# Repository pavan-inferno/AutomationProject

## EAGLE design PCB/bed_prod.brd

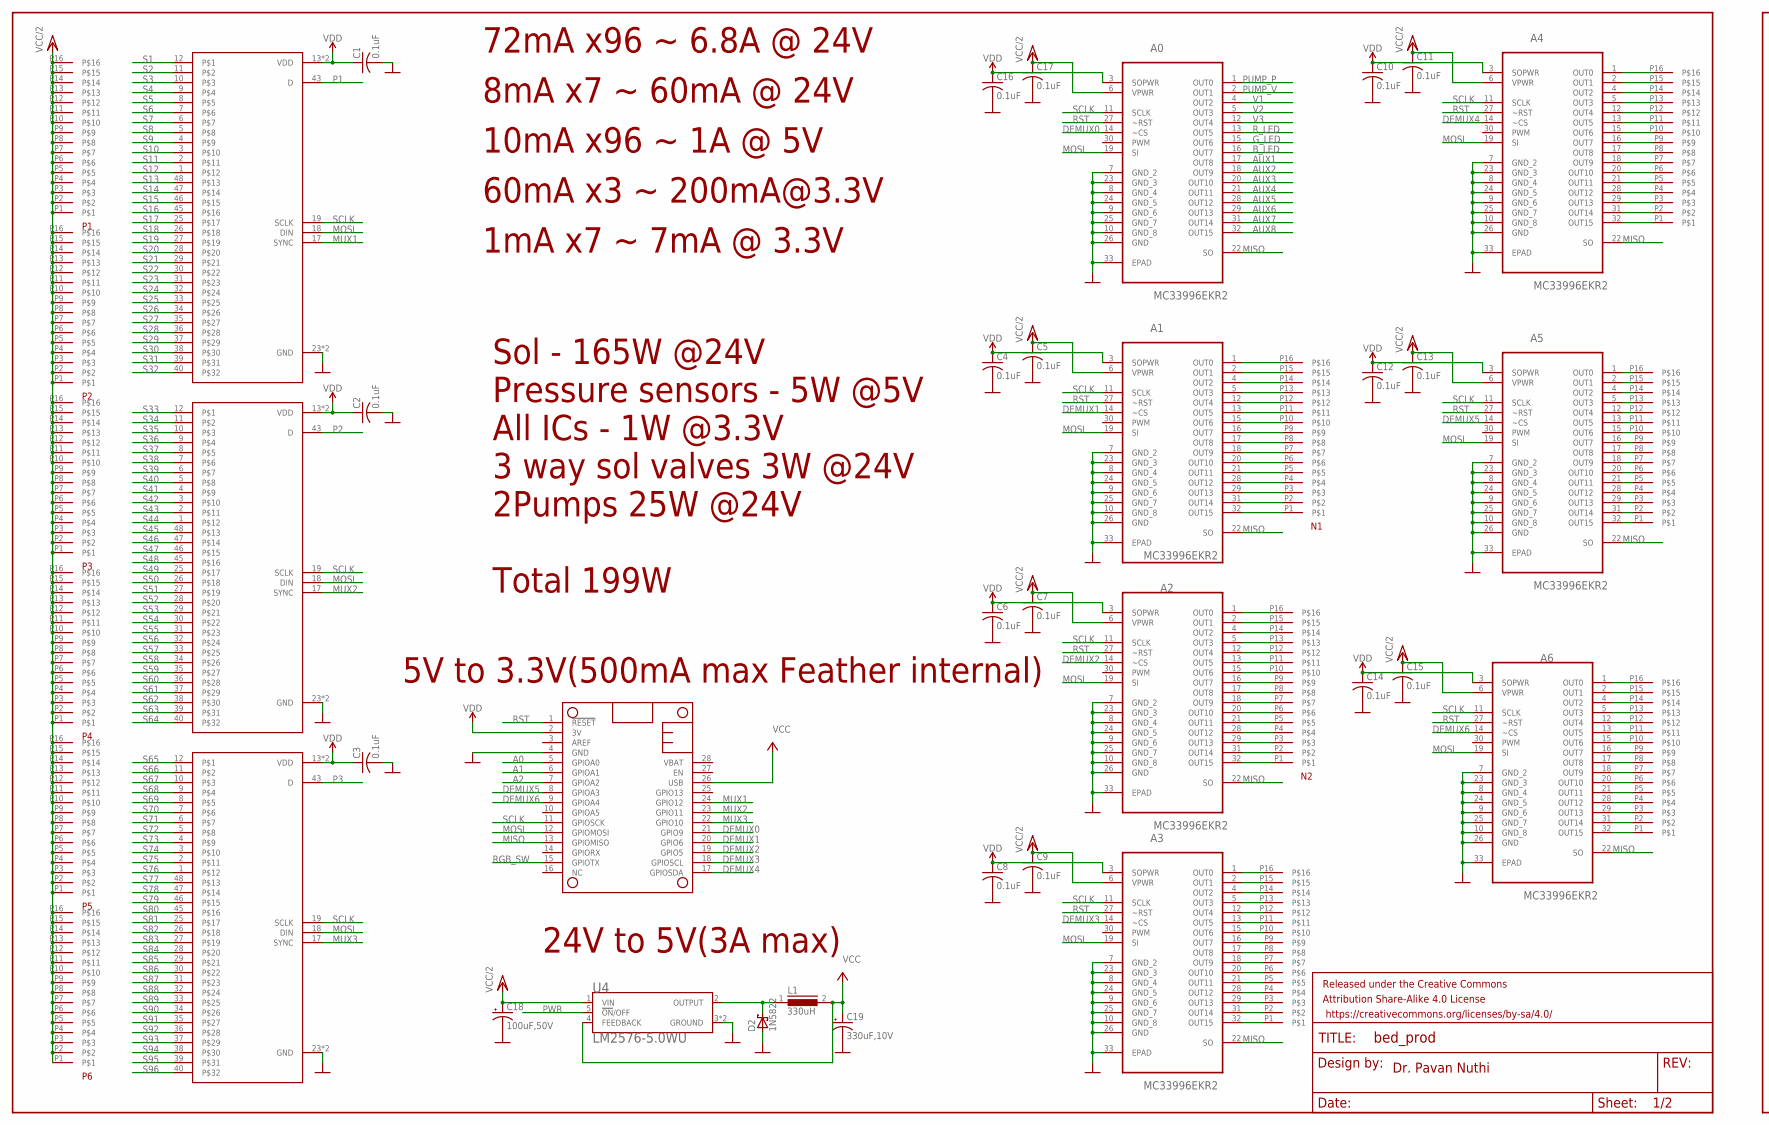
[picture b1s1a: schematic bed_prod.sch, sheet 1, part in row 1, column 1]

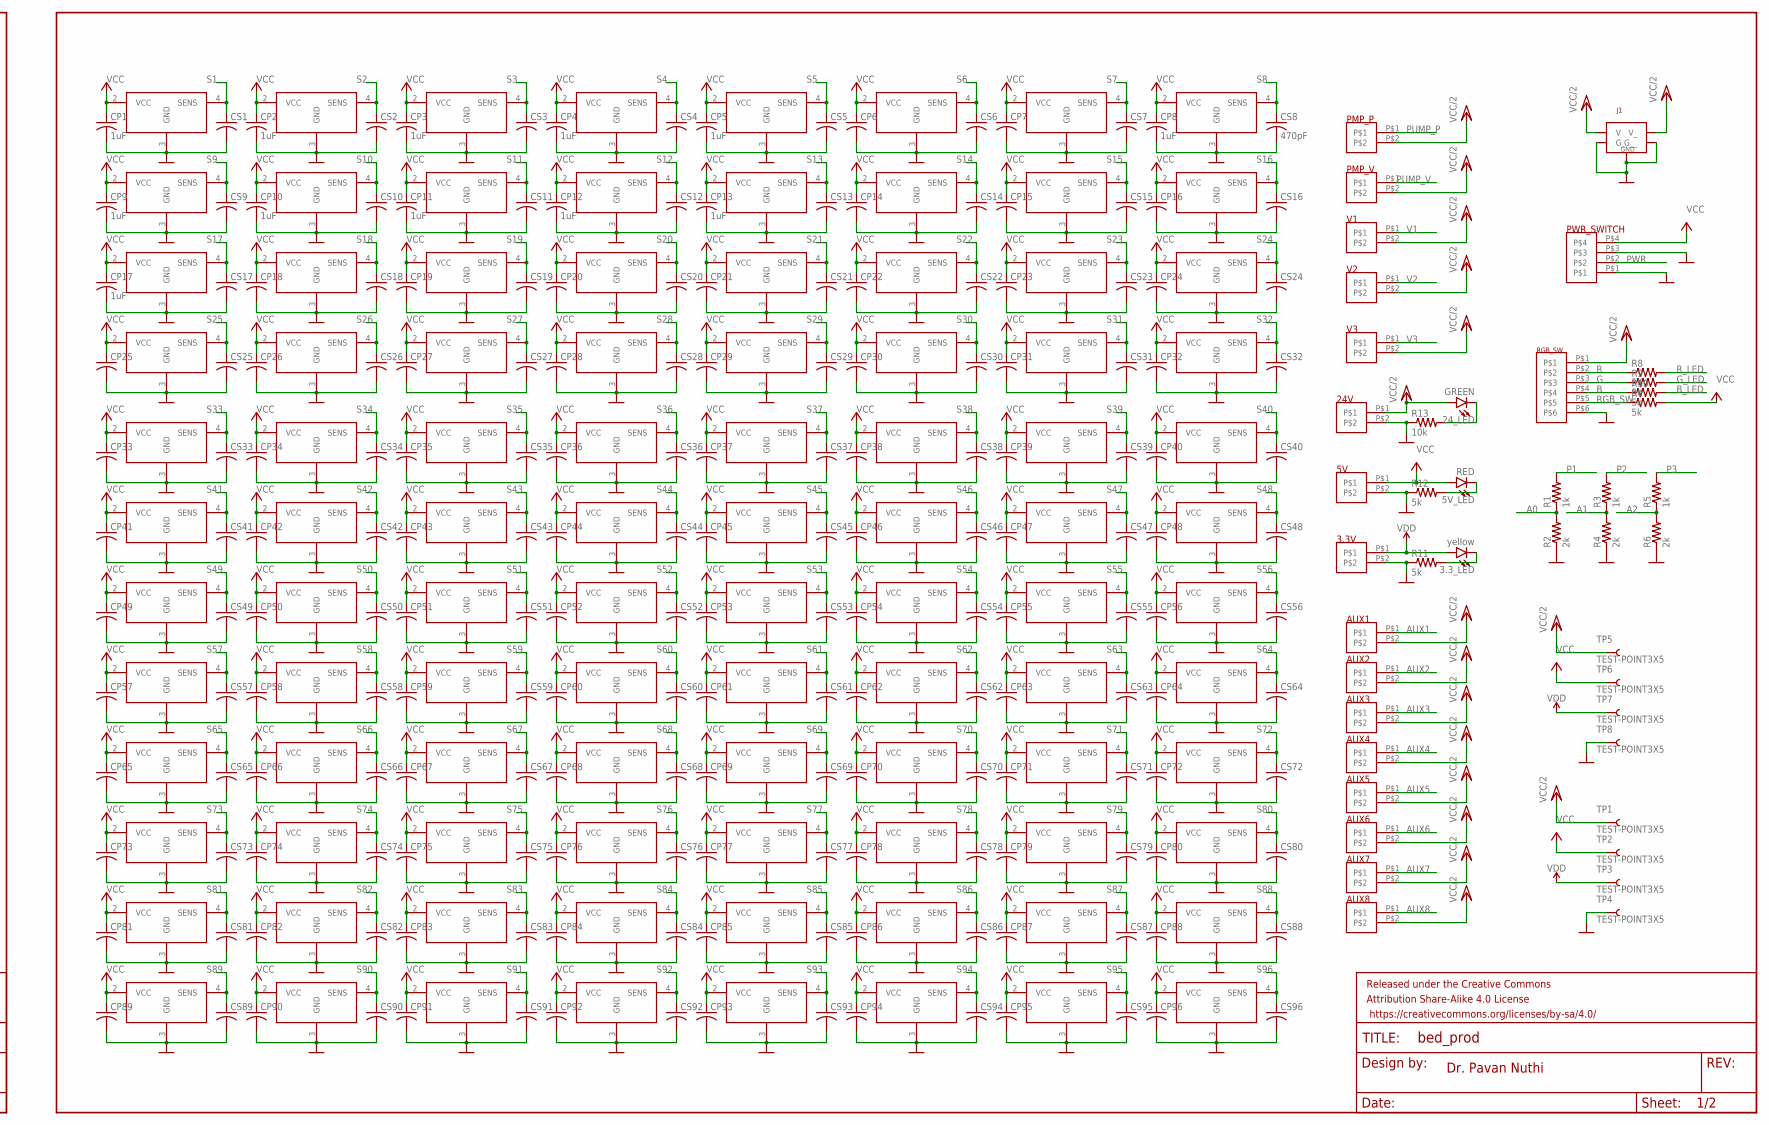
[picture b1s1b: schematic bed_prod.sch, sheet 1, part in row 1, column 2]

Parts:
3.3V, 5V, 24V: 2CONN_2MM
3.3_LED: yellow; LED-1206
5V_LED: RED; LED-1206
24_LED: GREEN; LED-1206
A0, A1, A2, A3, A4, A5, A6: MC33996EKR2; SOIC65P1030X265-32N
AUX1, AUX2, AUX3, AUX4, AUX5, AUX6, AUX7, AUX8: 2CONN_2MM
C1, C2, C3, C4, C5, C6, C7, C8, C9, C10, C11, C12, C13, C14, C15, C16, C17: 0.1uF; C1206
C18: 100uF,50V; E3,5-8
C19: 330uF,10V; E3,5-8
CP1, CP2, CP3, CP4, CP5, CP8, CP9, CP10, CP11, CP12, CP13, CP17: 1uF; C1206
CP6, CP7, CP14, CP15, CP16, CP18, CP19, CP20, CP21, CP22, CP23, CP24, CP25, CP26, CP27, CP28, CP29, CP30, CP31, CP32, CP33, CP34, CP35, CP36, CP37, CP38, CP39, CP40, CP41, CP42, CP43, CP44, CP45, CP46, CP47, CP48, CP49, CP50, CP51, CP52, CP53, CP54, CP55, CP56, CP57, CP58, CP59, CP60, CP61, CP62, CP63, CP64, CP65, CP66, CP67, CP68, CP69, CP70, CP71, CP72, CP73, CP74, CP75, CP76, CP77, CP78, CP79, CP80, CP81, CP82, CP83, CP84, CP85, CP86, CP87, CP88, CP89, CP90, CP91, CP92, CP93, CP94, CP95, CP96: C-USC1206; C1206
CS1, CS2, CS3, CS4, CS5, CS6, CS7, CS9, CS10, CS11, CS12, CS13, CS14, CS15, CS16, CS17, CS18, CS19, CS20, CS21, CS22, CS23, CS24, CS25, CS26, CS27, CS28, CS29, CS30, CS31, CS32, CS33, CS34, CS35, CS36, CS37, CS38, CS39, CS40, CS41, CS42, CS43, CS44, CS45, CS46, CS47, CS48, CS49, CS50, CS51, CS52, CS53, CS54, CS55, CS56, CS57, CS58, CS59, CS60, CS61, CS62, CS63, CS64, CS65, CS66, CS67, CS68, CS69, CS70, CS71, CS72, CS73, CS74, CS75, CS76, CS77, CS78, CS79, CS80, CS81, CS82, CS83, CS84, CS85, CS86, CS87, CS88, CS89, CS90, CS91, CS92, CS93, CS94, CS95, CS96: C-USC1206; C1206
CS8: 470pF; C1206
D2: 1N5822; DO201T15
FRAME1, FRAME2: FRAME-LEDGER; CREATIVE_COMMONS
J1: KPJX-4S-S; KYCON-KPXJ-4S
L1: 330uH; DR127
MS1: FEATHERWING_NODIM; FEATHERWING_DIM
N1, N2, N3, N4, N5, N6: 16CONN_2MM
P1, P2, P3, P4, P5, P6: 16CONN_2MM
PMP_P: 2CONN_2MM
PMP_V: 2CONN_2MM
PWR_SWITCH: 4CONN_2MM
R1, R3, R5: 1k; R1206
R2, R4, R6: 2k; R1206
R7, R9, R10, R11, R12: 5k; R1206W
R8: 5K; R1206W
R13: 10k; R1206W
RGB_SW: 6CONN_2MM
SENS1, SENS2, SENS3, SENS4, SENS5, SENS6, SENS7, SENS8, SENS9, SENS10, SENS11, SENS12, SENS13, SENS14, SENS15, SENS16, SENS17, SENS18, SENS19, SENS20, SENS21, SENS22, SENS23, SENS24, SENS25, SENS26, SENS27, SENS28, SENS29, SENS30, SENS31, SENS32, SENS33, SENS34, SENS35, SENS36, SENS37, SENS38, SENS39, SENS40, SENS41, SENS42, SENS43, SENS44, SENS45, SENS46, SENS47, SENS48, SENS49, SENS50, SENS51, SENS52, SENS53, SENS54, SENS55, SENS56, SENS57, SENS58, SENS59, SENS60, SENS61, SENS62, SENS63, SENS64, SENS65, SENS66, SENS67, SENS68, SENS69, SENS70, SENS71, SENS72, SENS73, SENS74, SENS75, SENS76, SENS77, SENS78, SENS79, SENS80, SENS81, SENS82, SENS83, SENS84, SENS85, SENS86, SENS87, SENS88, SENS89, SENS90, SENS91, SENS92, SENS93, SENS94, SENS95, SENS96: MPX5100; 98ASB17759C
TP1, TP2, TP3, TP4, TP5, TP6, TP7, TP8: TEST-POINT3X5; PAD.03X.05
U1, U2, U3: ADG731; QFP50P900X900X160-49N
U4: LM2576-5.0WU; DPAK6P170_1524X459L254X81N
V1, V2, V3: 2CONN_2MM

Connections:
A0: MS1.5 (GPIOA0), R1.1, R2.2
A1: MS1.6 (GPIOA1), R3.1, R4.2
A2: MS1.7 (GPIOA2), R5.1, R6.2
AUX1: A0.17 (OUT8), AUX1.P$1
AUX2: A0.18 (OUT9), AUX2.P$1
AUX3: A0.20 (OUT10), AUX3.P$1
AUX4: A0.21 (OUT11), AUX4.P$1
AUX5: A0.28 (OUT12), AUX5.P$1
AUX6: A0.29 (OUT13), AUX6.P$1
AUX7: A0.31 (OUT14), AUX7.P$1
AUX8: A0.32 (OUT15), AUX8.P$1
B: R10.1, RGB_SW.P$4
B_LED: A0.16 (OUT7), R10.2
DEMUX0: A0.14 (~CS), MS1.21 (GPIO9)
DEMUX1: A1.14 (~CS), MS1.20 (GPIO6)
DEMUX2: A2.14 (~CS), MS1.19 (GPIO5)
DEMUX3: A3.14 (~CS), MS1.18 (GPIOSCL)
DEMUX4: A4.14 (~CS), MS1.17 (GPIOSDA)
DEMUX5: A5.14 (~CS), MS1.8 (GPIOA3)
DEMUX6: A6.14 (~CS), MS1.9 (GPIOA4)
G: R9.1, RGB_SW.P$3
GND: 3.3V.P$2, 5V.P$2, 24V.P$2, A0.7 (GND_2), A0.8 (GND_4), A0.9 (GND_6), A0.10 (GND_8), A0.23 (GND_3), A0.24 (GND_5), A0.25 (GND_7), A0.26 (GND), A0.33 (EPAD), A1.7 (GND_2), A1.8 (GND_4), A1.9 (GND_6), A1.10 (GND_8), A1.23 (GND_3), A1.24 (GND_5), A1.25 (GND_7), A1.26 (GND), A1.33 (EPAD), A2.7 (GND_2), A2.8 (GND_4), A2.9 (GND_6), A2.10 (GND_8), A2.23 (GND_3), A2.24 (GND_5), A2.25 (GND_7), A2.26 (GND), A2.33 (EPAD), A3.7 (GND_2), A3.8 (GND_4), A3.9 (GND_6), A3.10 (GND_8), A3.23 (GND_3), A3.24 (GND_5), A3.25 (GND_7), A3.26 (GND), A3.33 (EPAD), A4.7 (GND_2), A4.8 (GND_4), A4.9 (GND_6), A4.10 (GND_8), A4.23 (GND_3), A4.24 (GND_5), A4.25 (GND_7), A4.26 (GND), A4.33 (EPAD), A5.7 (GND_2), A5.8 (GND_4), A5.9 (GND_6), A5.10 (GND_8), A5.23 (GND_3), A5.24 (GND_5), A5.25 (GND_7), A5.26 (GND), A5.33 (EPAD), A6.7 (GND_2), A6.8 (GND_4), A6.9 (GND_6), A6.10 (GND_8), A6.23 (GND_3), A6.24 (GND_5), A6.25 (GND_7), A6.26 (GND), A6.33 (EPAD), C1.2, C2.2, C3.2, C4.2, C5.2, C6.2, C7.2, C8.2, C9.2, C10.2, C11.2, C12.2, C13.2, C14.2, C15.2, C16.2, C17.2, C18.-, C19.-, CP1.2, CP2.2, CP3.2, CP4.2, CP5.2, CP6.2, CP7.2, CP8.2, CP9.2, CP10.2, CP11.2, CP12.2, CP13.2, CP14.2, CP15.2, CP16.2, CP17.2, CP18.2, CP19.2, CP20.2, CP21.2, CP22.2, CP23.2, CP24.2, CP25.2, CP26.2, CP27.2, CP28.2, CP29.2, CP30.2, CP31.2, CP32.2, CP33.2, CP34.2, CP35.2, CP36.2, CP37.2, CP38.2, CP39.2, CP40.2, CP41.2, CP42.2, CP43.2, CP44.2, CP45.2, CP46.2, CP47.2, CP48.2, CP49.2, CP50.2, CP51.2, CP52.2, CP53.2, CP54.2, CP55.2, CP56.2, CP57.2, CP58.2, CP59.2, CP60.2, CP61.2, CP62.2, CP63.2, CP64.2, CP65.2, CP66.2, CP67.2, CP68.2, CP69.2, CP70.2, CP71.2, CP72.2, CP73.2, CP74.2, CP75.2, CP76.2, CP77.2, CP78.2, CP79.2, CP80.2, CP81.2, CP82.2, CP83.2, CP84.2, CP85.2, CP86.2, CP87.2, CP88.2, CP89.2, CP90.2, CP91.2, CP92.2, CP93.2, CP94.2, CP95.2, CP96.2, CS1.2, CS2.2, CS3.2, CS4.2, CS5.2, CS6.2, CS7.2, CS8.2, CS9.2, CS10.2, CS11.2, CS12.2, CS13.2, CS14.2, CS15.2, CS16.2, CS17.2, CS18.2, CS19.2, CS20.2, CS21.2, CS22.2, CS23.2, CS24.2, CS25.2, CS26.2, CS27.2, CS28.2, CS29.2, CS30.2, CS31.2, CS32.2, CS33.2, CS34.2, CS35.2, CS36.2, CS37.2, CS38.2, CS39.2, CS40.2, CS41.2, CS42.2, CS43.2, CS44.2, CS45.2, CS46.2, CS47.2, CS48.2, CS49.2, CS50.2, CS51.2, CS52.2, CS53.2, CS54.2, CS55.2, CS56.2, CS57.2, CS58.2, CS59.2, CS60.2, CS61.2, CS62.2, CS63.2, CS64.2, CS65.2, CS66.2, CS67.2, CS68.2, CS69.2, CS70.2, CS71.2, CS72.2, CS73.2, CS74.2, CS75.2, CS76.2, CS77.2, CS78.2, CS79.2, CS80.2, CS81.2, CS82.2, CS83.2, CS84.2, CS85.2, CS86.2, CS87.2, CS88.2, CS89.2, CS90.2, CS91.2, CS92.2, CS93.2, CS94.2, CS95.2, CS96.2, D2.A, J1.GND (G), J1.GND_ (G_), J1.GND__ (G__), MS1.4 (GND), PWR_SWITCH.P$1, PWR_SWITCH.P$3, R2.1, R4.1, R6.1, R11.1, R12.1, R13.1, RGB_SW.P$6, SENS1.3 (GND), SENS2.3 (GND), SENS3.3 (GND), SENS4.3 (GND), SENS5.3 (GND), SENS6.3 (GND), SENS7.3 (GND), SENS8.3 (GND), SENS9.3 (GND), SENS10.3 (GND), SENS11.3 (GND), SENS12.3 (GND), SENS13.3 (GND), SENS14.3 (GND), SENS15.3 (GND), SENS16.3 (GND), SENS17.3 (GND), SENS18.3 (GND), SENS19.3 (GND), SENS20.3 (GND), SENS21.3 (GND), SENS22.3 (GND), SENS23.3 (GND), SENS24.3 (GND), SENS25.3 (GND), SENS26.3 (GND), SENS27.3 (GND), SENS28.3 (GND), SENS29.3 (GND), SENS30.3 (GND), SENS31.3 (GND), SENS32.3 (GND), SENS33.3 (GND), SENS34.3 (GND), SENS35.3 (GND), SENS36.3 (GND), SENS37.3 (GND), SENS38.3 (GND), SENS39.3 (GND), SENS40.3 (GND), SENS41.3 (GND), SENS42.3 (GND), SENS43.3 (GND), SENS44.3 (GND), SENS45.3 (GND), SENS46.3 (GND), SENS47.3 (GND), SENS48.3 (GND), SENS49.3 (GND), SENS50.3 (GND), SENS51.3 (GND), SENS52.3 (GND), SENS53.3 (GND), SENS54.3 (GND), SENS55.3 (GND), SENS56.3 (GND), SENS57.3 (GND), SENS58.3 (GND), SENS59.3 (GND), SENS60.3 (GND), SENS61.3 (GND), SENS62.3 (GND), SENS63.3 (GND), SENS64.3 (GND), SENS65.3 (GND), SENS66.3 (GND), SENS67.3 (GND), SENS68.3 (GND), SENS69.3 (GND), SENS70.3 (GND), SENS71.3 (GND), SENS72.3 (GND), SENS73.3 (GND), SENS74.3 (GND), SENS75.3 (GND), SENS76.3 (GND), SENS77.3 (GND), SENS78.3 (GND), SENS79.3 (GND), SENS80.3 (GND), SENS81.3 (GND), SENS82.3 (GND), SENS83.3 (GND), SENS84.3 (GND), SENS85.3 (GND), SENS86.3 (GND), SENS87.3 (GND), SENS88.3 (GND), SENS89.3 (GND), SENS90.3 (GND), SENS91.3 (GND), SENS92.3 (GND), SENS93.3 (GND), SENS94.3 (GND), SENS95.3 (GND), SENS96.3 (GND), TP4.P$1, TP8.P$1, U1.23 (GND), U1.24 (GND), U2.23 (GND), U2.24 (GND), U3.23 (GND), U3.24 (GND), U4.3 (GROUND), U4.6 (GROUND)
G_LED: A0.15 (OUT6), R9.2
MISO: A0.22 (SO), A1.22 (SO), A2.22 (SO), A3.22 (SO), A4.22 (SO), A5.22 (SO), A6.22 (SO), MS1.13 (GPIOMISO)
MOSI: A0.19 (SI), A1.19 (SI), A2.19 (SI), A3.19 (SI), A4.19 (SI), A5.19 (SI), A6.19 (SI), MS1.12 (GPIOMOSI), U1.18 (DIN), U2.18 (DIN), U3.18 (DIN)
MUX1: MS1.24 (GPIO12), U1.17 (SYNC)
MUX2: MS1.23 (GPIO11), U2.17 (SYNC)
MUX3: MS1.22 (GPIO10), U3.17 (SYNC)
unnamed: D2.C, L1.1, U4.2 (OUTPUT)
unnamed: A5.1 (OUT0), N5.P16
unnamed: A5.2 (OUT1), N5.P15
unnamed: A5.4 (OUT2), N5.P14
unnamed: A5.5 (OUT3), N5.P13
unnamed: A5.12 (OUT4), N5.P12
unnamed: A5.13 (OUT5), N5.P11
unnamed: A5.15 (OUT6), N5.P10
unnamed: A5.16 (OUT7), N5.P9
unnamed: A5.17 (OUT8), N5.P8
unnamed: A5.18 (OUT9), N5.P7
unnamed: A5.20 (OUT10), N5.P6
unnamed: A5.21 (OUT11), N5.P5
unnamed: A5.28 (OUT12), N5.P4
unnamed: A5.29 (OUT13), N5.P3
unnamed: A5.31 (OUT14), N5.P2
unnamed: A5.32 (OUT15), N5.P1
unnamed: A6.1 (OUT0), N6.P16
unnamed: A6.2 (OUT1), N6.P15
unnamed: A6.4 (OUT2), N6.P14
unnamed: A6.5 (OUT3), N6.P13
unnamed: A6.12 (OUT4), N6.P12
unnamed: A6.13 (OUT5), N6.P11
unnamed: A6.15 (OUT6), N6.P10
unnamed: A6.16 (OUT7), N6.P9
unnamed: A6.17 (OUT8), N6.P8
unnamed: A6.18 (OUT9), N6.P7
unnamed: A6.20 (OUT10), N6.P6
unnamed: A6.21 (OUT11), N6.P5
unnamed: A6.28 (OUT12), N6.P4
unnamed: A6.29 (OUT13), N6.P3
unnamed: A6.31 (OUT14), N6.P2
unnamed: A6.32 (OUT15), N6.P1
unnamed: A4.1 (OUT0), N4.P16
unnamed: A4.2 (OUT1), N4.P15
unnamed: A4.4 (OUT2), N4.P14
unnamed: A4.5 (OUT3), N4.P13
unnamed: A4.12 (OUT4), N4.P12
unnamed: A4.13 (OUT5), N4.P11
unnamed: A4.15 (OUT6), N4.P10
unnamed: A4.16 (OUT7), N4.P9
unnamed: A4.17 (OUT8), N4.P8
unnamed: A4.18 (OUT9), N4.P7
unnamed: A4.20 (OUT10), N4.P6
unnamed: A4.21 (OUT11), N4.P5
unnamed: A4.28 (OUT12), N4.P4
unnamed: A4.29 (OUT13), N4.P3
unnamed: A4.31 (OUT14), N4.P2
unnamed: A4.32 (OUT15), N4.P1
unnamed: A3.1 (OUT0), N3.P16
unnamed: A3.2 (OUT1), N3.P15
unnamed: A3.4 (OUT2), N3.P14
unnamed: A3.5 (OUT3), N3.P13
unnamed: A3.12 (OUT4), N3.P12
unnamed: A3.13 (OUT5), N3.P11
unnamed: A3.15 (OUT6), N3.P10
unnamed: A3.16 (OUT7), N3.P9
unnamed: A3.17 (OUT8), N3.P8
unnamed: A3.18 (OUT9), N3.P7
unnamed: A3.20 (OUT10), N3.P6
unnamed: A3.21 (OUT11), N3.P5
unnamed: A3.28 (OUT12), N3.P4
unnamed: A3.29 (OUT13), N3.P3
unnamed: A3.31 (OUT14), N3.P2
unnamed: A1.1 (OUT0), N1.P16
unnamed: A1.2 (OUT1), N1.P15
unnamed: A1.4 (OUT2), N1.P14
unnamed: A1.5 (OUT3), N1.P13
unnamed: A1.12 (OUT4), N1.P12
unnamed: A1.13 (OUT5), N1.P11
unnamed: A1.15 (OUT6), N1.P10
unnamed: A1.16 (OUT7), N1.P9
unnamed: A1.17 (OUT8), N1.P8
unnamed: A1.18 (OUT9), N1.P7
unnamed: A1.20 (OUT10), N1.P6
unnamed: A1.21 (OUT11), N1.P5
unnamed: A1.28 (OUT12), N1.P4
unnamed: A1.29 (OUT13), N1.P3
unnamed: A1.31 (OUT14), N1.P2
unnamed: A1.32 (OUT15), N1.P1
unnamed: A2.1 (OUT0), N2.P16
unnamed: A2.2 (OUT1), N2.P15
unnamed: A2.4 (OUT2), N2.P14
unnamed: A2.5 (OUT3), N2.P13
unnamed: A2.12 (OUT4), N2.P12
unnamed: A2.13 (OUT5), N2.P11
unnamed: A2.15 (OUT6), N2.P10
unnamed: A2.16 (OUT7), N2.P9
unnamed: A2.17 (OUT8), N2.P8
unnamed: A2.18 (OUT9), N2.P7
unnamed: A2.20 (OUT10), N2.P6
unnamed: A2.21 (OUT11), N2.P5
unnamed: A2.28 (OUT12), N2.P4
unnamed: A2.29 (OUT13), N2.P3
unnamed: A2.31 (OUT14), N2.P2
unnamed: A2.32 (OUT15), N2.P1
unnamed: 3.3_LED.C, R11.2
unnamed: 24_LED.C, R13.2
unnamed: 5V_LED.C, R12.2
unnamed: A3.32 (OUT15), N3.P1
P1: R1.2, U1.43 (D)
P2: R3.2, U2.43 (D)
P3: R5.2, U3.43 (D)
PUMP_P: A0.1 (OUT0), PMP_P.P$1
PUMP_V: A0.2 (OUT1), PMP_V.P$1
PWR: PWR_SWITCH.P$2, U4.5 (!ON!/OFF)
R: R8.1, RGB_SW.P$2
RGB_SW: MS1.15 (GPIOTX), R7.1, RGB_SW.P$5
RST: A0.27 (~RST), A1.27 (~RST), A2.27 (~RST), A3.27 (~RST), A4.27 (~RST), A5.27 (~RST), A6.27 (~RST), MS1.1 (!RESET)
R_LED: A0.13 (OUT5), R8.2
S1: CS1.1, SENS1.4 (SENS), U1.12
S2: CS2.1, SENS2.4 (SENS), U1.11
S3: CS3.1, SENS3.4 (SENS), U1.10
S4: CS4.1, SENS4.4 (SENS), U1.9
S5: CS5.1, SENS5.4 (SENS), U1.8
S6: CS6.1, SENS6.4 (SENS), U1.7
S7: CS7.1, SENS7.4 (SENS), U1.6
S8: CS8.1, SENS8.4 (SENS), U1.5
S9: CS9.1, SENS9.4 (SENS), U1.4
S10: CS10.1, SENS10.4 (SENS), U1.3
S11: CS11.1, SENS11.4 (SENS), U1.2
S12: CS12.1, SENS12.4 (SENS), U1.1
S13: CS13.1, SENS13.4 (SENS), U1.48
S14: CS14.1, SENS14.4 (SENS), U1.47
S15: CS15.1, SENS15.4 (SENS), U1.46
S16: CS16.1, SENS16.4 (SENS), U1.45
S17: CS17.1, SENS17.4 (SENS), U1.25
S18: CS18.1, SENS18.4 (SENS), U1.26
S19: CS19.1, SENS19.4 (SENS), U1.27
S20: CS20.1, SENS20.4 (SENS), U1.28
S21: CS21.1, SENS21.4 (SENS), U1.29
S22: CS22.1, SENS22.4 (SENS), U1.30
S23: CS23.1, SENS23.4 (SENS), U1.31
S24: CS24.1, SENS24.4 (SENS), U1.32
S25: CS25.1, SENS25.4 (SENS), U1.33
S26: CS26.1, SENS26.4 (SENS), U1.34
S27: CS27.1, SENS27.4 (SENS), U1.35
S28: CS28.1, SENS28.4 (SENS), U1.36
S29: CS29.1, SENS29.4 (SENS), U1.37
S30: CS30.1, SENS30.4 (SENS), U1.38
S31: CS31.1, SENS31.4 (SENS), U1.39
S32: CS32.1, SENS32.4 (SENS), U1.40
S33: CS33.1, SENS33.4 (SENS), U2.12
S34: CS34.1, SENS34.4 (SENS), U2.11
S35: CS35.1, SENS35.4 (SENS), U2.10
S36: CS36.1, SENS36.4 (SENS), U2.9
S37: CS37.1, SENS37.4 (SENS), U2.8
S38: CS38.1, SENS38.4 (SENS), U2.7
S39: CS39.1, SENS39.4 (SENS), U2.6
S40: CS40.1, SENS40.4 (SENS), U2.5
S41: CS41.1, SENS41.4 (SENS), U2.4
S42: CS42.1, SENS42.4 (SENS), U2.3
S43: CS43.1, SENS43.4 (SENS), U2.2
S44: CS44.1, SENS44.4 (SENS), U2.1
S45: CS45.1, SENS45.4 (SENS), U2.48
S46: CS46.1, SENS46.4 (SENS), U2.47
S47: CS47.1, SENS47.4 (SENS), U2.46
S48: CS48.1, SENS48.4 (SENS), U2.45
S49: CS49.1, SENS49.4 (SENS), U2.25
S50: CS50.1, SENS50.4 (SENS), U2.26
S51: CS51.1, SENS51.4 (SENS), U2.27
S52: CS52.1, SENS52.4 (SENS), U2.28
S53: CS53.1, SENS53.4 (SENS), U2.29
S54: CS54.1, SENS54.4 (SENS), U2.30
S55: CS55.1, SENS55.4 (SENS), U2.31
S56: CS56.1, SENS56.4 (SENS), U2.32
S57: CS57.1, SENS57.4 (SENS), U2.33
S58: CS58.1, SENS58.4 (SENS), U2.34
S59: CS59.1, SENS59.4 (SENS), U2.35
S60: CS60.1, SENS60.4 (SENS), U2.36
S61: CS61.1, SENS61.4 (SENS), U2.37
S62: CS62.1, SENS62.4 (SENS), U2.38
S63: CS63.1, SENS63.4 (SENS), U2.39
S64: CS64.1, SENS64.4 (SENS), U2.40
S65: CS65.1, SENS65.4 (SENS), U3.12
S66: CS66.1, SENS66.4 (SENS), U3.11
S67: CS67.1, SENS67.4 (SENS), U3.10
S68: CS68.1, SENS68.4 (SENS), U3.9
S69: CS69.1, SENS69.4 (SENS), U3.8
S70: CS70.1, SENS70.4 (SENS), U3.7
S71: CS71.1, SENS71.4 (SENS), U3.6
S72: CS72.1, SENS72.4 (SENS), U3.5
S73: CS73.1, SENS73.4 (SENS), U3.4
S74: CS74.1, SENS74.4 (SENS), U3.3
S75: CS75.1, SENS75.4 (SENS), U3.2
S76: CS76.1, SENS76.4 (SENS), U3.1
S77: CS77.1, SENS77.4 (SENS), U3.48
S78: CS78.1, SENS78.4 (SENS), U3.47
S79: CS79.1, SENS79.4 (SENS), U3.46
S80: CS80.1, SENS80.4 (SENS), U3.45
S81: CS81.1, SENS81.4 (SENS), U3.25
S82: CS82.1, SENS82.4 (SENS), U3.26
S83: CS83.1, SENS83.4 (SENS), U3.27
S84: CS84.1, SENS84.4 (SENS), U3.28
S85: CS85.1, SENS85.4 (SENS), U3.29
S86: CS86.1, SENS86.4 (SENS), U3.30
S87: CS87.1, SENS87.4 (SENS), U3.31
S88: CS88.1, SENS88.4 (SENS), U3.32
S89: CS89.1, SENS89.4 (SENS), U3.33
S90: CS90.1, SENS90.4 (SENS), U3.34
S91: CS91.1, SENS91.4 (SENS), U3.35
S92: CS92.1, SENS92.4 (SENS), U3.36
S93: CS93.1, SENS93.4 (SENS), U3.37
S94: CS94.1, SENS94.4 (SENS), U3.38
S95: CS95.1, SENS95.4 (SENS), U3.39
S96: CS96.1, SENS96.4 (SENS), U3.40
SCLK: A0.11 (SCLK), A1.11 (SCLK), A2.11 (SCLK), A3.11 (SCLK), A4.11 (SCLK), A5.11 (SCLK), A6.11 (SCLK), MS1.11 (GPIOSCK), U1.19 (SCLK), U2.19 (SCLK), U3.19 (SCLK)
V1: A0.4 (OUT2), V1.P$1
V2: A0.5 (OUT3), V2.P$1
V3: A0.12 (OUT4), V3.P$1
VCC: 5V.P$1, 5V_LED.A, C19.+, CP1.1, CP2.1, CP3.1, CP4.1, CP5.1, CP6.1, CP7.1, CP8.1, CP9.1, CP10.1, CP11.1, CP12.1, CP13.1, CP14.1, CP15.1, CP16.1, CP17.1, CP18.1, CP19.1, CP20.1, CP21.1, CP22.1, CP23.1, CP24.1, CP25.1, CP26.1, CP27.1, CP28.1, CP29.1, CP30.1, CP31.1, CP32.1, CP33.1, CP34.1, CP35.1, CP36.1, CP37.1, CP38.1, CP39.1, CP40.1, CP41.1, CP42.1, CP43.1, CP44.1, CP45.1, CP46.1, CP47.1, CP48.1, CP49.1, CP50.1, CP51.1, CP52.1, CP53.1, CP54.1, CP55.1, CP56.1, CP57.1, CP58.1, CP59.1, CP60.1, CP61.1, CP62.1, CP63.1, CP64.1, CP65.1, CP66.1, CP67.1, CP68.1, CP69.1, CP70.1, CP71.1, CP72.1, CP73.1, CP74.1, CP75.1, CP76.1, CP77.1, CP78.1, CP79.1, CP80.1, CP81.1, CP82.1, CP83.1, CP84.1, CP85.1, CP86.1, CP87.1, CP88.1, CP89.1, CP90.1, CP91.1, CP92.1, CP93.1, CP94.1, CP95.1, CP96.1, L1.2, MS1.26 (USB), PWR_SWITCH.P$4, R7.2, SENS1.2 (VCC), SENS2.2 (VCC), SENS3.2 (VCC), SENS4.2 (VCC), SENS5.2 (VCC), SENS6.2 (VCC), SENS7.2 (VCC), SENS8.2 (VCC), SENS9.2 (VCC), SENS10.2 (VCC), SENS11.2 (VCC), SENS12.2 (VCC), SENS13.2 (VCC), SENS14.2 (VCC), SENS15.2 (VCC), SENS16.2 (VCC), SENS17.2 (VCC), SENS18.2 (VCC), SENS19.2 (VCC), SENS20.2 (VCC), SENS21.2 (VCC), SENS22.2 (VCC), SENS23.2 (VCC), SENS24.2 (VCC), SENS25.2 (VCC), SENS26.2 (VCC), SENS27.2 (VCC), SENS28.2 (VCC), SENS29.2 (VCC), SENS30.2 (VCC), SENS31.2 (VCC), SENS32.2 (VCC), SENS33.2 (VCC), SENS34.2 (VCC), SENS35.2 (VCC), SENS36.2 (VCC), SENS37.2 (VCC), SENS38.2 (VCC), SENS39.2 (VCC), SENS40.2 (VCC), SENS41.2 (VCC), SENS42.2 (VCC), SENS43.2 (VCC), SENS44.2 (VCC), SENS45.2 (VCC), SENS46.2 (VCC), SENS47.2 (VCC), SENS48.2 (VCC), SENS49.2 (VCC), SENS50.2 (VCC), SENS51.2 (VCC), SENS52.2 (VCC), SENS53.2 (VCC), SENS54.2 (VCC), SENS55.2 (VCC), SENS56.2 (VCC), SENS57.2 (VCC), SENS58.2 (VCC), SENS59.2 (VCC), SENS60.2 (VCC), SENS61.2 (VCC), SENS62.2 (VCC), SENS63.2 (VCC), SENS64.2 (VCC), SENS65.2 (VCC), SENS66.2 (VCC), SENS67.2 (VCC), SENS68.2 (VCC), SENS69.2 (VCC), SENS70.2 (VCC), SENS71.2 (VCC), SENS72.2 (VCC), SENS73.2 (VCC), SENS74.2 (VCC), SENS75.2 (VCC), SENS76.2 (VCC), SENS77.2 (VCC), SENS78.2 (VCC), SENS79.2 (VCC), SENS80.2 (VCC), SENS81.2 (VCC), SENS82.2 (VCC), SENS83.2 (VCC), SENS84.2 (VCC), SENS85.2 (VCC), SENS86.2 (VCC), SENS87.2 (VCC), SENS88.2 (VCC), SENS89.2 (VCC), SENS90.2 (VCC), SENS91.2 (VCC), SENS92.2 (VCC), SENS93.2 (VCC), SENS94.2 (VCC), SENS95.2 (VCC), SENS96.2 (VCC), TP2.P$1, TP6.P$1, U4.4 (FEEDBACK)
VCC/2: 24V.P$1, 24_LED.A, A0.6 (VPWR), A1.6 (VPWR), A2.6 (VPWR), A3.6 (VPWR), A4.6 (VPWR), A5.6 (VPWR), A6.6 (VPWR), AUX1.P$2, AUX2.P$2, AUX3.P$2, AUX4.P$2, AUX5.P$2, AUX6.P$2, AUX7.P$2, AUX8.P$2, C5.1, C7.1, C9.1, C11.1, C13.1, C15.1, C17.1, C18.+, J1.V+ (V), J1.V++ (V_), P1.P1, P1.P2, P1.P3, P1.P4, P1.P5, P1.P6, P1.P7, P1.P8, P1.P9, P1.P10, P1.P11, P1.P12, P1.P13, P1.P14, P1.P15, P1.P16, P2.P1, P2.P2, P2.P3, P2.P4, P2.P5, P2.P6, P2.P7, P2.P8, P2.P9, P2.P10, P2.P11, P2.P12, P2.P13, P2.P14, P2.P15, P2.P16, P3.P1, P3.P2, P3.P3, P3.P4, P3.P5, P3.P6, P3.P7, P3.P8, P3.P9, P3.P10, P3.P11, P3.P12, P3.P13, P3.P14, P3.P15, P3.P16, P4.P1, P4.P2, P4.P3, P4.P4, P4.P5, P4.P6, P4.P7, P4.P8, P4.P9, P4.P10, P4.P11, P4.P12, P4.P13, P4.P14, P4.P15, P4.P16, P5.P1, P5.P2, P5.P3, P5.P4, P5.P5, P5.P6, P5.P7, P5.P8, P5.P9, P5.P10, P5.P11, P5.P12, P5.P13, P5.P14, P5.P15, P5.P16, P6.P1, P6.P2, P6.P3, P6.P4, P6.P5, P6.P6, P6.P7, P6.P8, P6.P9, P6.P10, P6.P11, P6.P12, P6.P13, P6.P14, P6.P15, P6.P16, PMP_P.P$2, PMP_V.P$2, RGB_SW.P$1, TP1.P$1, TP5.P$1, U4.1 (VIN), V1.P$2, V2.P$2, V3.P$2
VDD: 3.3V.P$1, 3.3_LED.A, A0.3 (SOPWR), A1.3 (SOPWR), A2.3 (SOPWR), A3.3 (SOPWR), A4.3 (SOPWR), A5.3 (SOPWR), A6.3 (SOPWR), C1.1, C2.1, C3.1, C4.1, C6.1, C8.1, C10.1, C12.1, C14.1, C16.1, MS1.2 (3V), TP3.P$1, TP7.P$1, U1.13 (VDD), U1.14 (VDD), U2.13 (VDD), U2.14 (VDD), U3.13 (VDD), U3.14 (VDD)

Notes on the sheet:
10mA x96 ~ 1A @ 5V
60mA x3 ~ 200mA@3.3V
8mA x7 ~ 60mA @ 24V
1mA x7 ~ 7mA @ 3.3V
24V to 5V(3A max)
5V to 3.3V(500mA max Feather internal)
72mA x96 ~ 6.8A @ 24V
Sol - 165W @24V Pressure sensors - 5W @5V All ICs - 1W @3.3V 3 way sol valves 3W @24V 2Pumps 25W @24V Total 199W
Dr. Pavan Nuthi

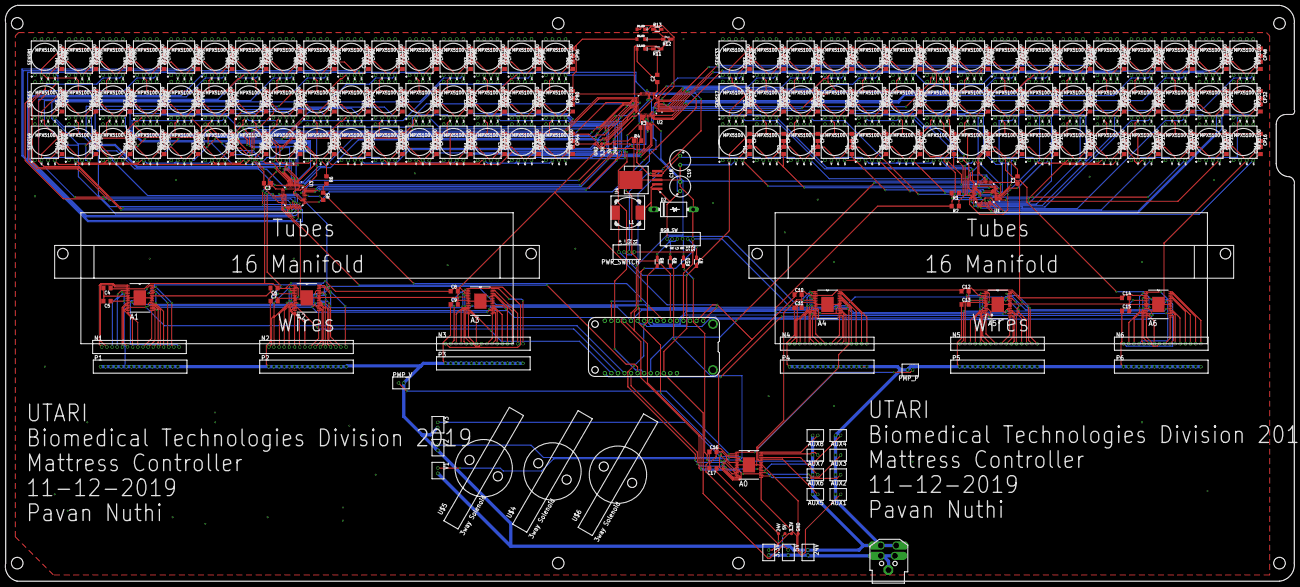
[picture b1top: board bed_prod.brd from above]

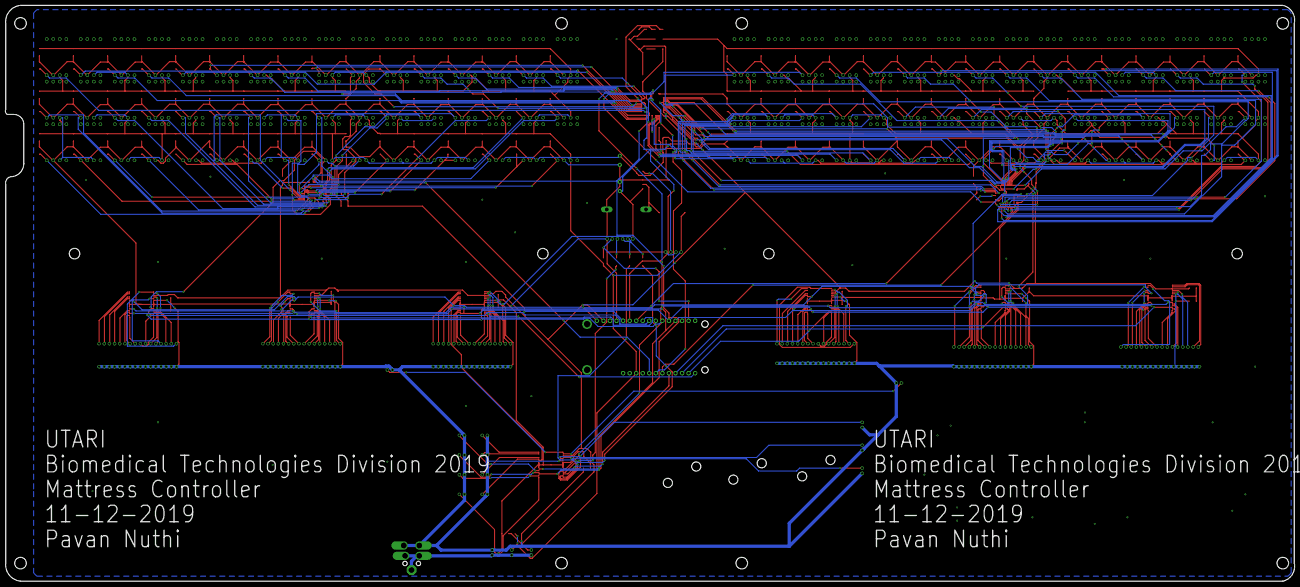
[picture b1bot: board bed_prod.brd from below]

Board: 2 copper layers, 500.0 x 223.3 mm, 384 parts (2 on the bottom side), 241 nets.

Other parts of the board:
U$1, U$3: MANIFOLD16
U$2: PTS-25349-C
U$4, U$5, U$6: EVO-3-24

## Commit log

2020-02-03 Exported project

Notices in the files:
parts and their libraries:
SparkFun-Connectors: Licensing: Creative Commons ShareAlike 4.0 International - https://creativecommons.org/licenses/by-sa/4.0
SparkFun-Aesthetics: Released under the Creative Commons Attribution Share-Alike 4.0 License
SparkFun-Aesthetics: https://creativecommons.org/licenses/by-sa/4.0
